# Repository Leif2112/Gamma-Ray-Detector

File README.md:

# Gamma Ray Detector

Open-source SiPM + scintillator gamma-ray detector designed for CubeSat payloads and lab use. The project refines the Pi-Pico [Open Gamma Detector] into a higher-fidelity instrument with an upgraded TIA, low-noise photodiode bias, and temperature-compensated SiPM operation.

> **Project status:** electronics and simulations complete; prototype assembly and environmental testing outstanding.

## Project output
- **Space focus:** tailored for CubeSat constraints.  
- **Cleaner analogue front-end:** OPA355 TIA selected for faster slew and lower noise than OPA357.  
- **Stable SiPM bias:** LT3571-based photodiode bias supply with low ripple and temperature compensation strategy.  
- **Thermal robustness:** overvoltage held constant vs temperature to stabilise SiPM gain/PDE.

---

## High-level objectives

1. Develop a CubeSat-compatible system by enhancing the Pi-Pico DIY detector  
2. Build a working prototype  
3. Test detection performance and space suitability

## Architecture

- [visual diagram]

- [ ] [Visuals]

## Features

- [ ] [Features list]

## Hardware

- [ ] [Hardware description]

## Firmware

- [ ] [Firmware dir.]

## Authors and acknowledgment

If you use this project in academic work, please cite the MSc thesis and this repository:
Tinwell, L. (2023). Gamma Ray Detector (MSc Thesis, University of Surrey).

***

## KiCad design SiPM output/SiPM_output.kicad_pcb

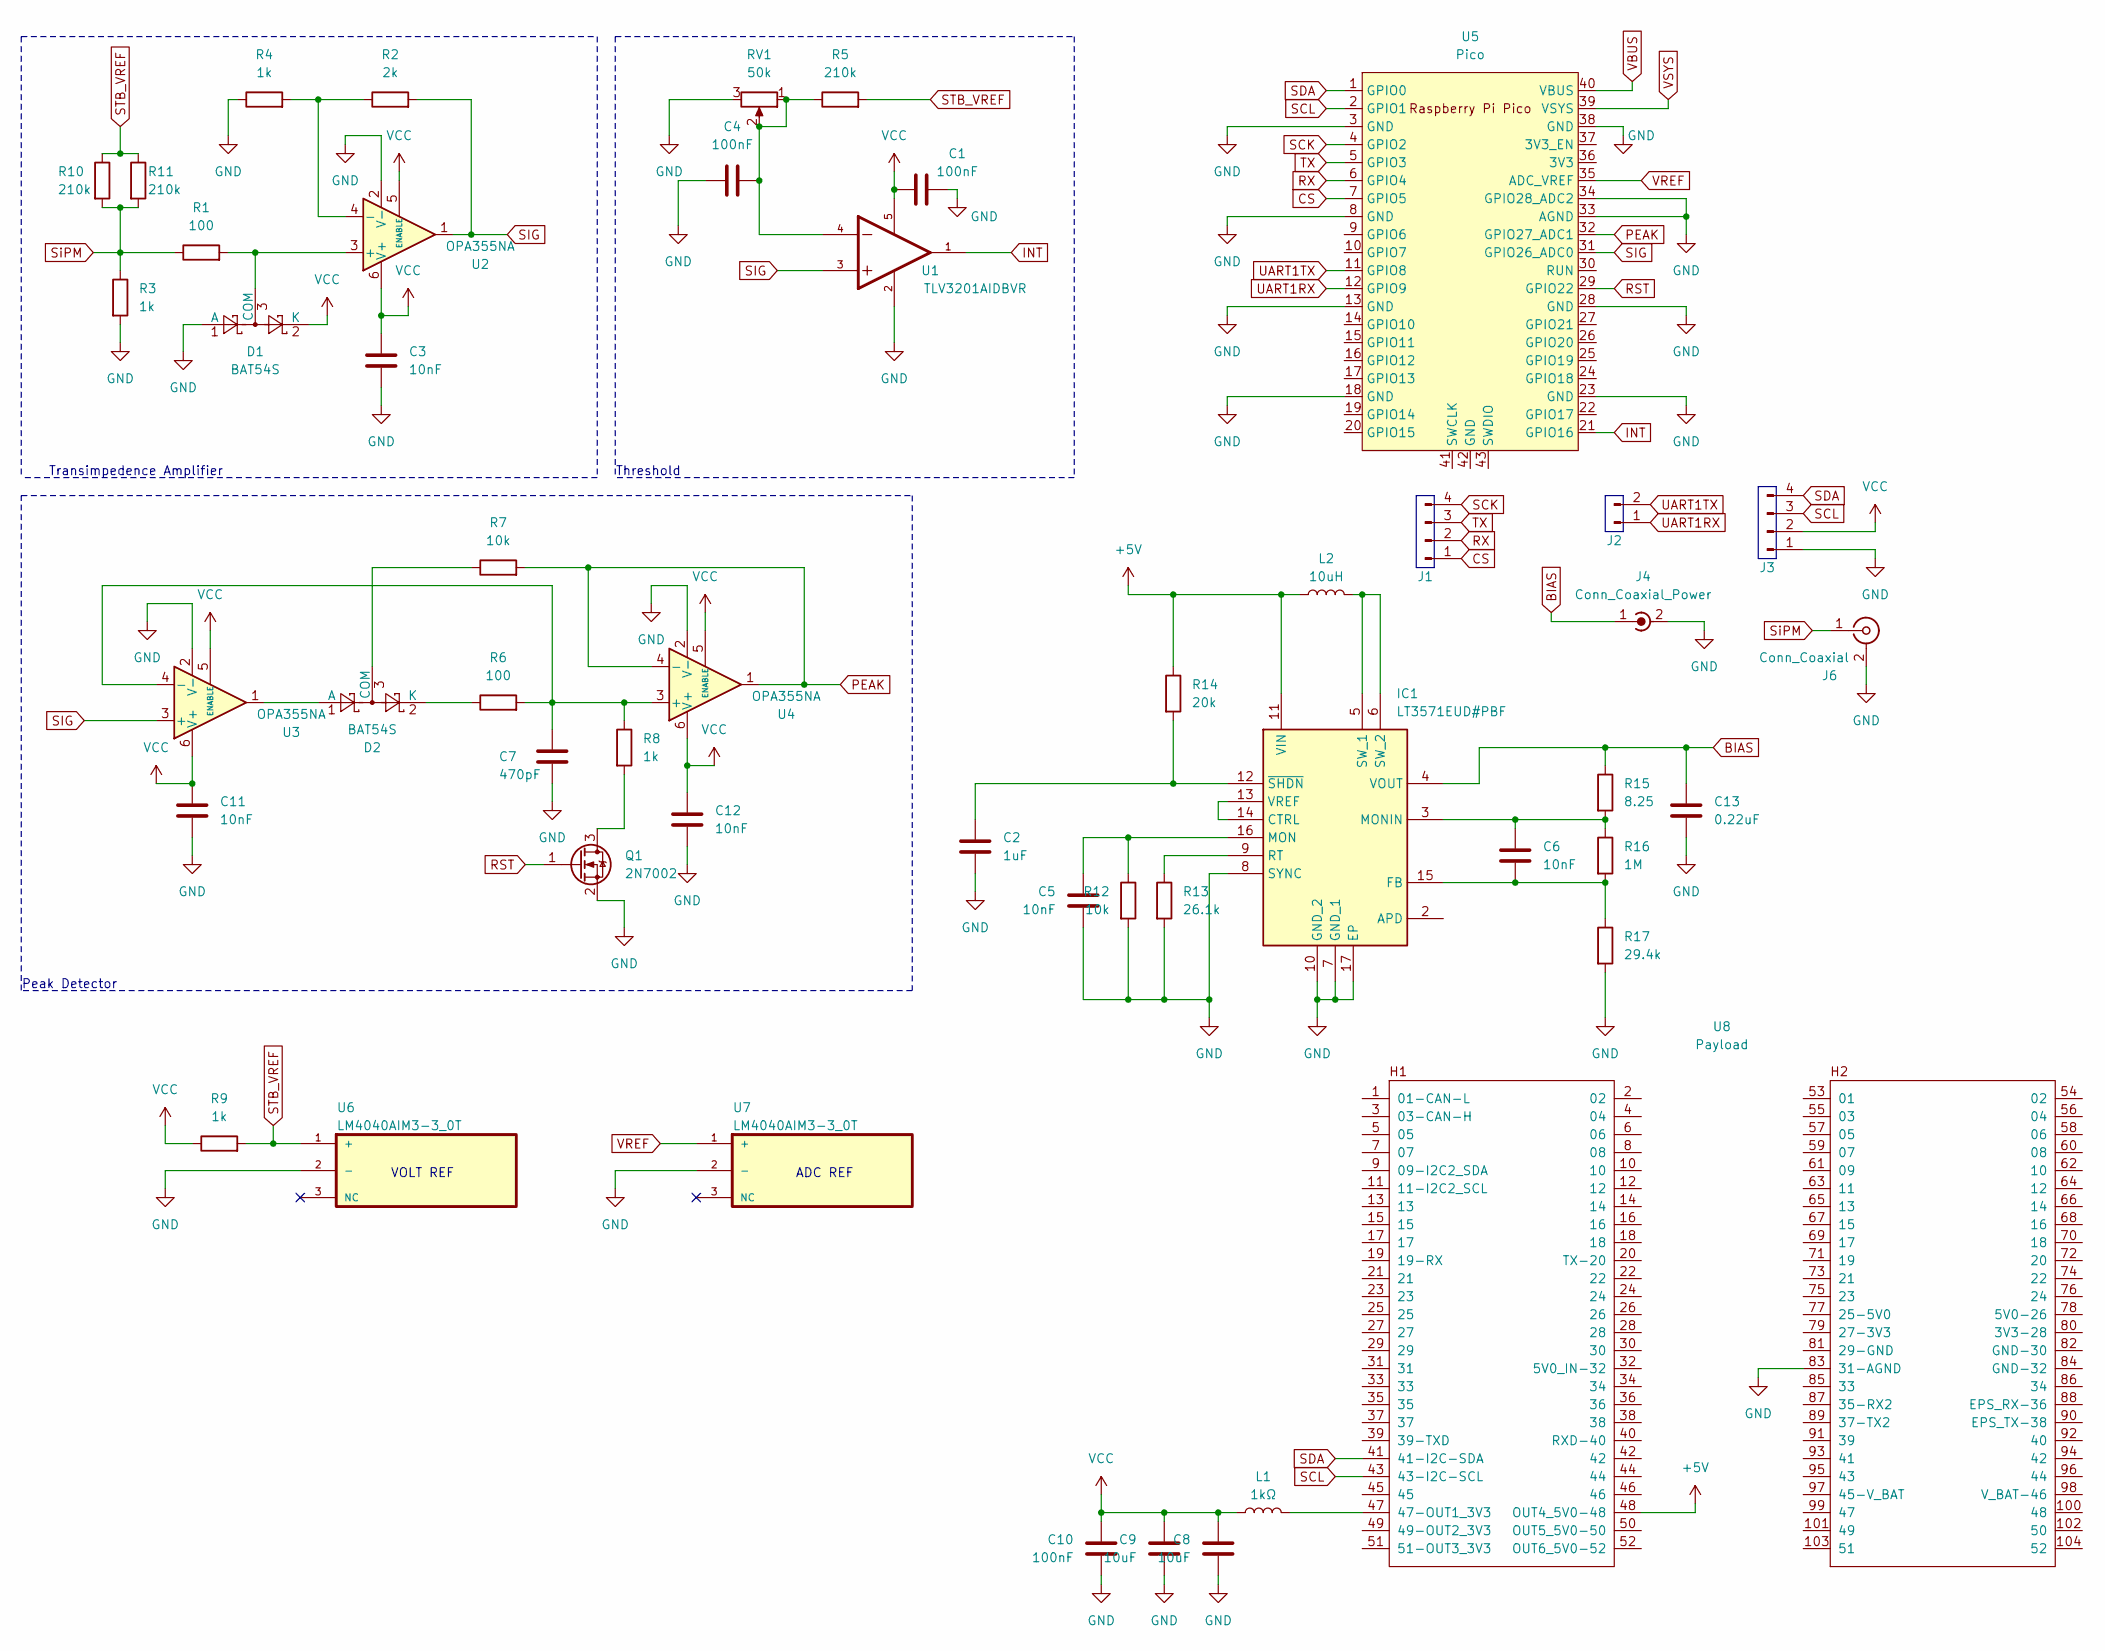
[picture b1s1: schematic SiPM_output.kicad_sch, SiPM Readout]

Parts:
C1, C4, C10: 100nF; C_0603_1608Metric
C2: 1uF; C_0603_1608Metric
C3, C5, C6, C11, C12: 10nF; C_0603_1608Metric
C7: 470pF; C_0603_1608Metric
C8, C9: 10uF; C_0603_1608Metric
C13: 0.22uF; C_0603_1608Metric
D1, D2: BAT54S; SOT-23
IC1: LT3571EUD#PBF; QFN50P300X300X80-17N-D
J1, J3: Conn_01x04_Pin; PinHeader_1x04_P2.54mm_Vertical
J2: Conn_01x02_Pin; PinHeader_1x02_P2.54mm_Vertical
J4: Conn_Coaxial_Power; SMA_Amphenol_132134-14_Vertical
J6: Conn_Coaxial; SMA_Amphenol_132134-14_Vertical
L1: 1kΩ; L_0603_1608Metric
L2: 10uH; L_Bourns_SRP7028A_7.3x6.6mm
Q1: 2N7002; SOT-23
R1, R6: 100; R_0603_1608Metric
R2: 2k; R_0603_1608Metric
R3, R4, R8, R9: 1k; R_0603_1608Metric
R5, R10, R11: 210k; R_0603_1608Metric
R7, R12: 10k; R_0603_1608Metric
R13: 26.1k; R_0603_1608Metric
R14: 20k; R_0603_1608Metric
R15: 8.25; R_0603_1608Metric
R16: 1M; R_0603_1608Metric
R17: 29.4k; R_0603_1608Metric
RV1: 50k; Potentiometer_Bourns_3296X_Horizontal
U1: TLV3201AIDBVR; SOT95P280X145-5N
U2, U3, U4: OPA355NA; SOT-23-6
U5: Pico; RPi_Pico_SMD_TH
U6, U7: LM4040AIM3-3_0T; SOT95P237X112-3N
U8: Payload; PC104-Standard

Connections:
+5V: IC1.11 (VIN), L2.1, R14.1, U8.48 (OUT4_5V0-48)
BIAS: C13.1, IC1.4 (VOUT), J4.1 (In), R15.1
CS: J1.1, U5.7 (GPIO5)
GND: C1.2, C2.2, C3.2, C4.1, C5.2, C7.2, C8.2, C9.2, C10.2, C11.2, C12.2, C13.2, D1.1 (A), IC1.7 (GND_1), IC1.8 (SYNC), IC1.10 (GND_2), IC1.17 (EP), J3.1, J4.2 (Ext), J6.2 (Ext), Q1.2 (S), R3.2, R4.1, R12.2, R13.2, R17.2, RV1.3, U1.2, U2.2 (V-), U3.2 (V-), U4.2 (V-), U5.3 (GND), U5.8 (GND), U5.13 (GND), U5.18 (GND), U5.23 (GND), U5.28 (GND), U5.33 (AGND), U5.34 (GPIO28_ADC2), U5.38 (GND), U6.2 (-), U7.2 (-), U8.83 (31-AGND)
INT: U1.1, U5.21 (GPIO16)
unnamed: C4.2, R5.1, RV1.1, RV1.2, U1.4
unnamed: D1.3 (COM), R1.2, U2.3 (+)
unnamed: D2.1 (A), U3.1
unnamed: D2.3 (COM), R7.1
unnamed: D2.2 (K), R6.1
unnamed: IC1.13 (VREF), IC1.14 (CTRL)
unnamed: C6.2, IC1.15 (FB), R16.2, R17.1
unnamed: C5.1, IC1.16 (MON), R12.1
unnamed: C6.1, IC1.3 (MONIN), R15.2, R16.1
unnamed: IC1.9 (RT), R13.1
unnamed: IC1.5 (SW_1), IC1.6 (SW_2), L2.2
unnamed: C2.1, IC1.12 (~SHDN), R14.2
unnamed: Q1.3 (D), R8.2
unnamed: R2.1, R4.2, U2.4 (-)
unnamed: C7.1, R6.2, R8.1, U3.4 (-), U4.3 (+)
unnamed: L1.1, U8.47 (47-OUT1_3V3)
PEAK: R7.2, U4.1, U4.4 (-), U5.32 (GPIO27_ADC1)
RST: Q1.1 (G), U5.29 (GPIO22)
RX: J1.2, U5.6 (GPIO4)
SCK: J1.4, U5.4 (GPIO2)
SCL: J3.3, U5.2 (GPIO1), U8.43 (43-I2C-SCL)
SDA: J3.4, U5.1 (GPIO0), U8.41 (41-I2C-SDA)
SIG: R2.2, U1.3, U2.1, U3.3 (+), U5.31 (GPIO26_ADC0)
STB_VREF: R5.2, R9.2, R10.1, R11.1, U6.1 (+)
SiPM: J6.1 (In), R1.1, R3.1, R10.2, R11.2
TX: J1.3, U5.5 (GPIO3)
UART1RX: J2.1, U5.12 (GPIO9)
UART1TX: J2.2, U5.11 (GPIO8)
VBUS: U5.40 (VBUS)
VCC: C1.1, C3.1, C8.1, C9.1, C10.1, C11.1, C12.1, D1.2 (K), J3.2, L1.2, R9.1, U1.5, U2.5 (ENABLE), U2.6 (V+), U3.5 (ENABLE), U3.6 (V+), U4.5 (ENABLE), U4.6 (V+)
VREF: U5.35 (ADC_VREF), U7.1 (+)
VSYS: U5.39 (VSYS)

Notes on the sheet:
Threshold
VOLT REF
Transimpedence Amplifier
Peak Detector
ADC REF

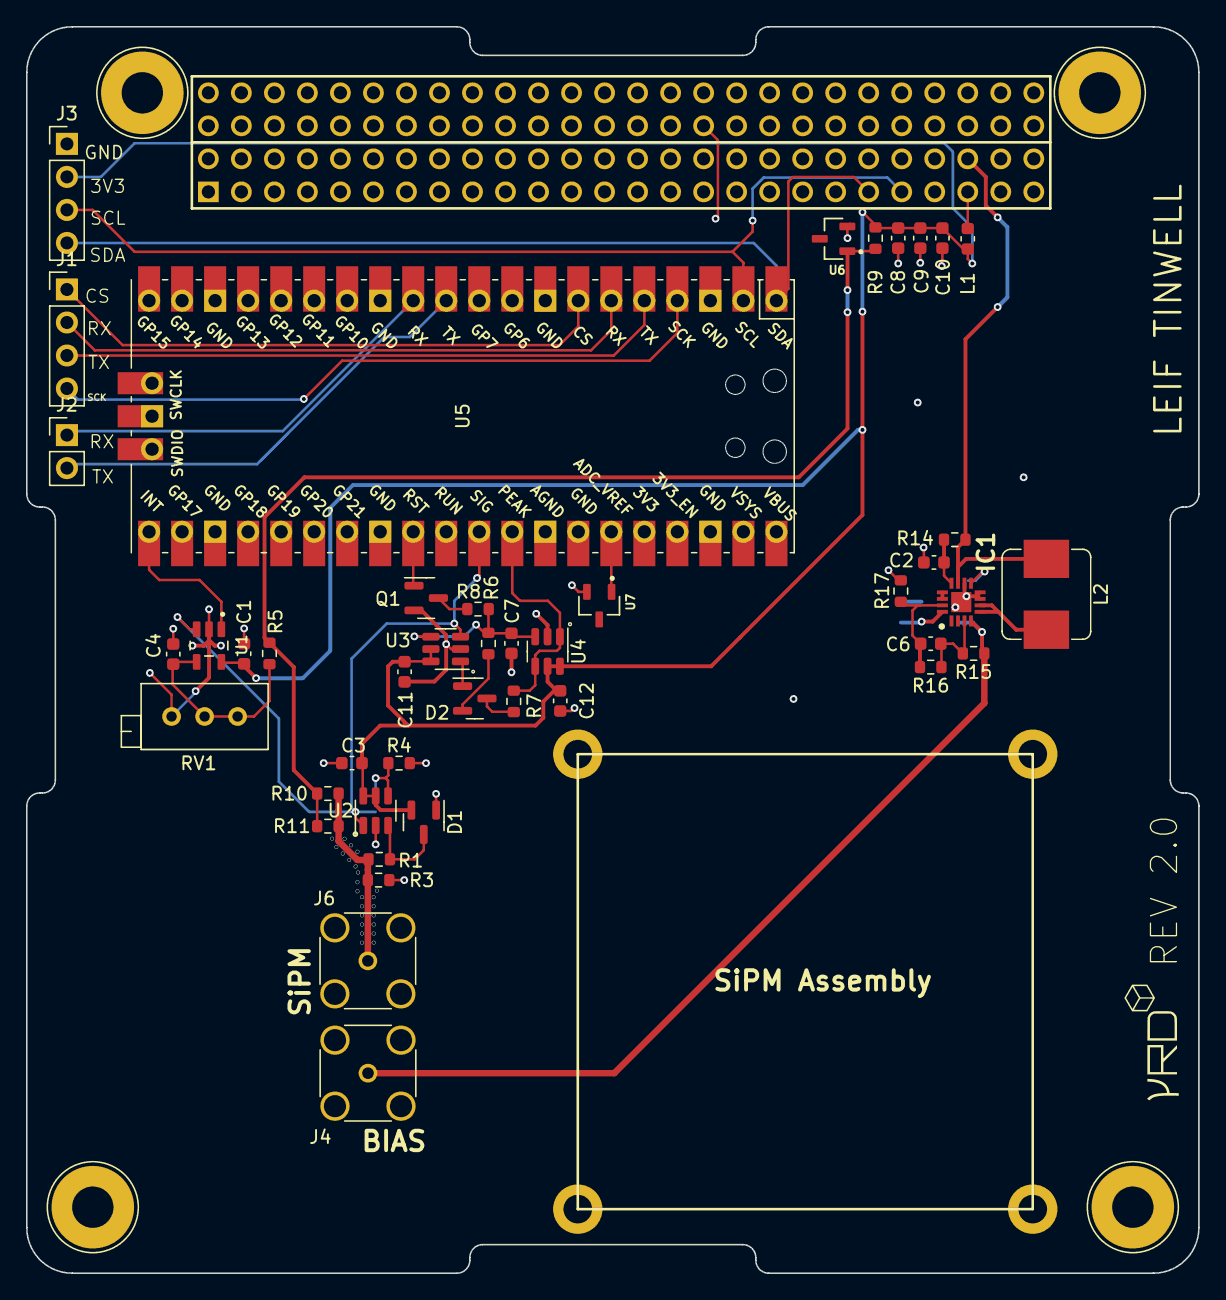
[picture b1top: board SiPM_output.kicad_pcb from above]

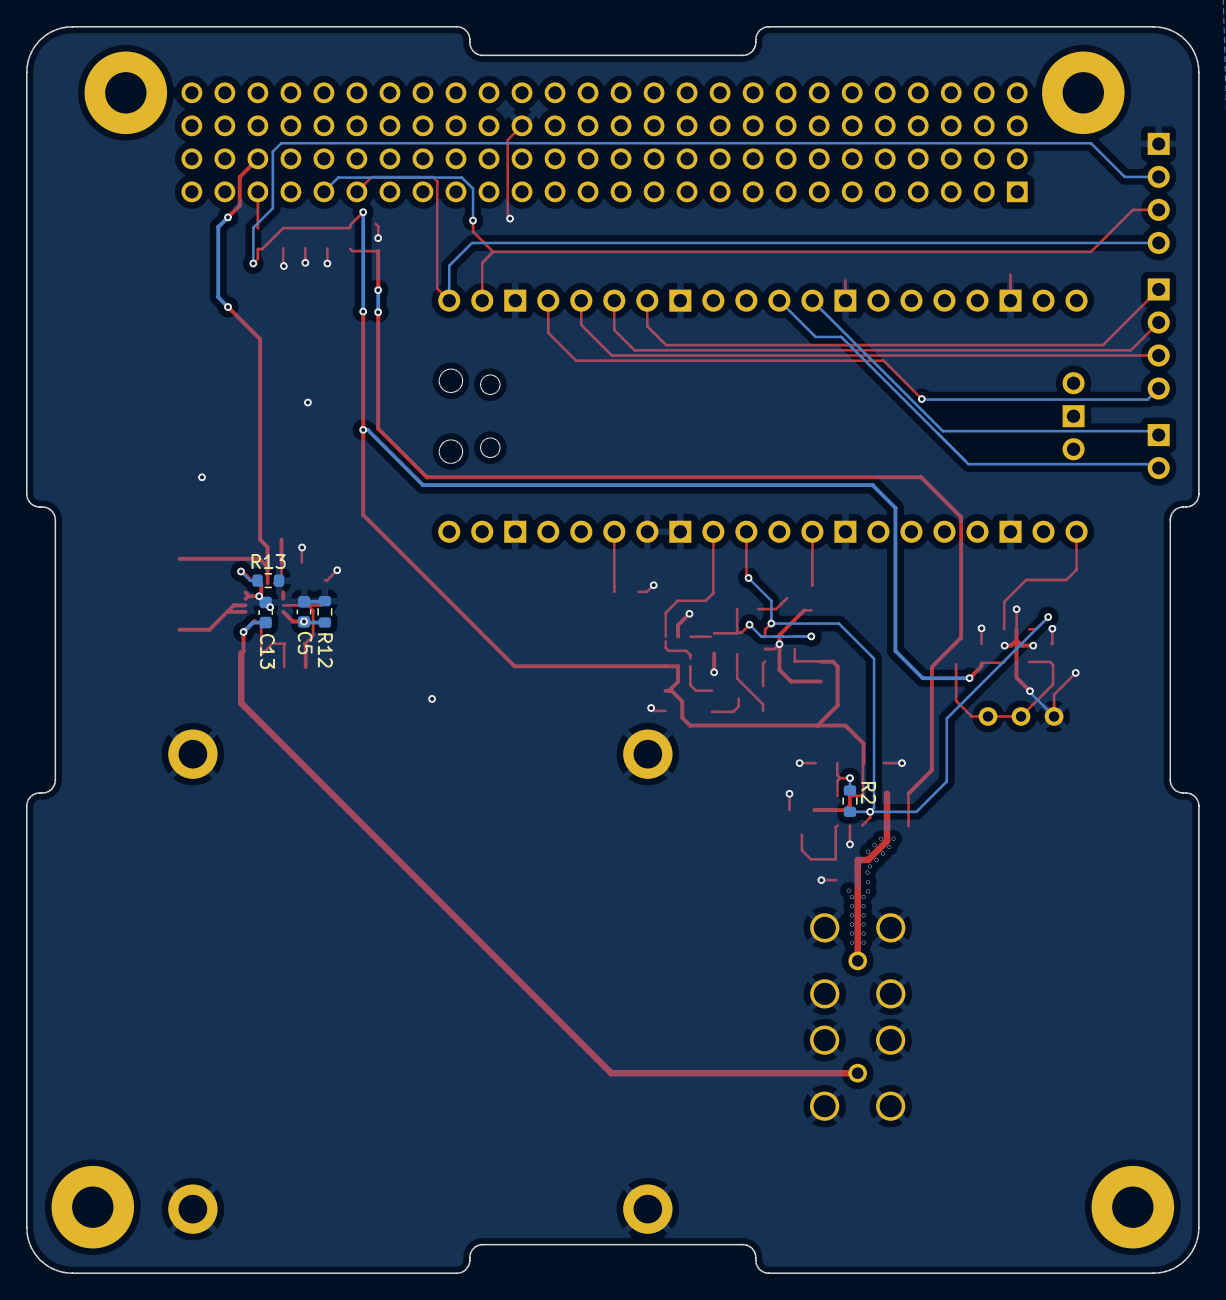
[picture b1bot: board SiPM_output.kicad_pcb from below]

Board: 2 copper layers, 90.2 x 95.9 mm, 50 parts (5 on the bottom side), 35 nets.

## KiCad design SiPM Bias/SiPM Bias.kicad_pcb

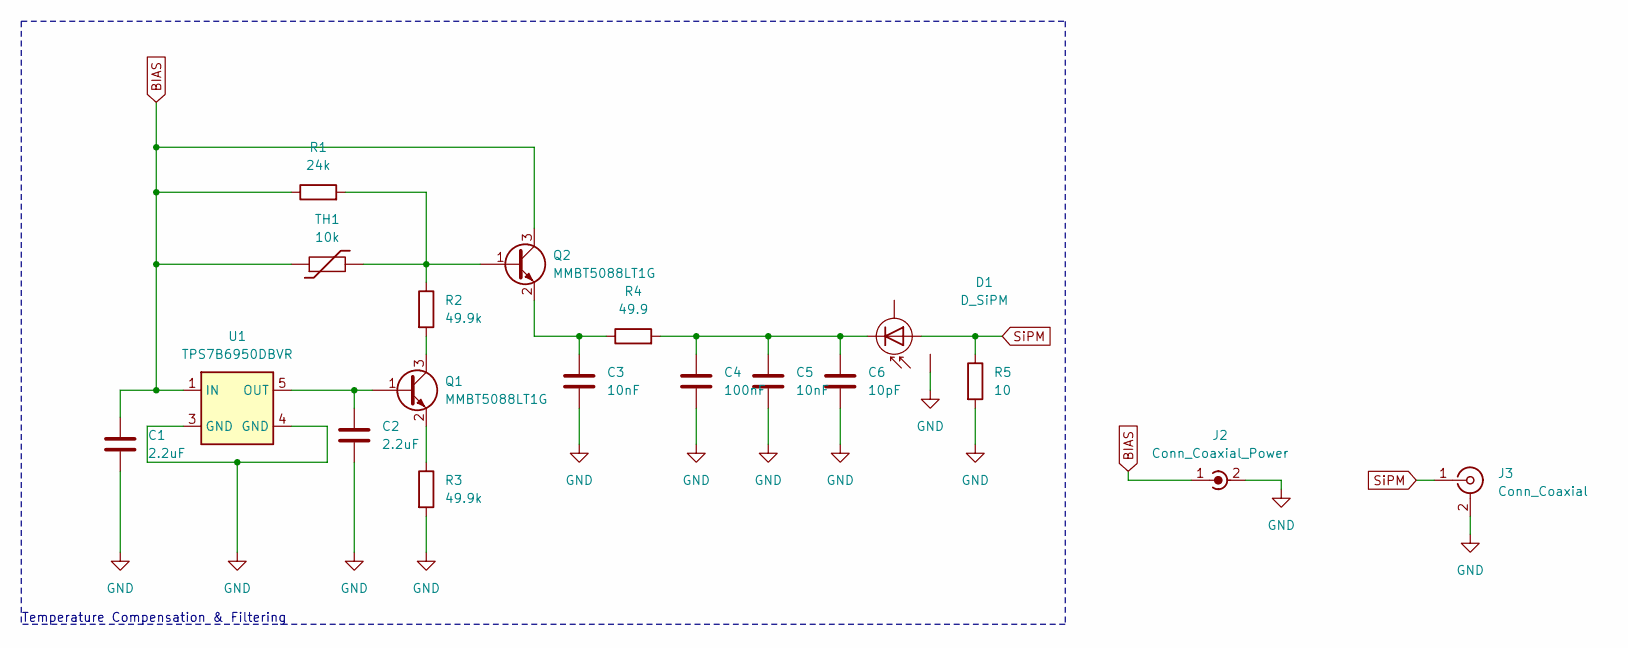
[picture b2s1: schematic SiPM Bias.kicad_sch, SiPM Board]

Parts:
C1, C2: 2.2uF; C_0603_1608Metric
C3, C5: 10nF; C_0603_1608Metric
C4: 100nF; C_0603_1608Metric
C6: 10pF; C_0603_1608Metric
D1: D_SiPM; MICROFC-60035
J2: Conn_Coaxial_Power; SMA_Amphenol_132134-14_Vertical
J3: Conn_Coaxial; SMA_Amphenol_132134-14_Vertical
Q1, Q2: MMBT5088LT1G; SOT-23-3
R1: 24k; R_0603_1608Metric
R2, R3: 49.9k; R_0603_1608Metric
R4: 49.9; R_0603_1608Metric
R5: 10; R_0603_1608Metric
TH1: 10k; R_0603_1608Metric
U1: TPS7B6950DBVR; SOT-23-5

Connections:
BIAS: C1.1, J2.1 (In), Q2.3 (C), R1.1, TH1.1, U1.1 (IN)
GND: C1.2, C2.2, C3.2, C4.2, C5.2, C6.2, D1.4 (G), J2.2 (Ext), J3.2 (Ext), R3.2, R5.2, U1.3 (GND), U1.4 (GND)
unnamed: C4.1, C5.1, C6.1, D1.3 (C), R4.2
unnamed: C2.1, Q1.1 (B), U1.5 (OUT)
unnamed: Q1.3 (C), R2.2
unnamed: Q1.2 (E), R3.1
unnamed: Q2.1 (B), R1.2, R2.1, TH1.2
unnamed: C3.1, Q2.2 (E), R4.1
SiPM: D1.1 (A), J3.1 (In), R5.1

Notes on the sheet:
Temperature Compensation & Filtering

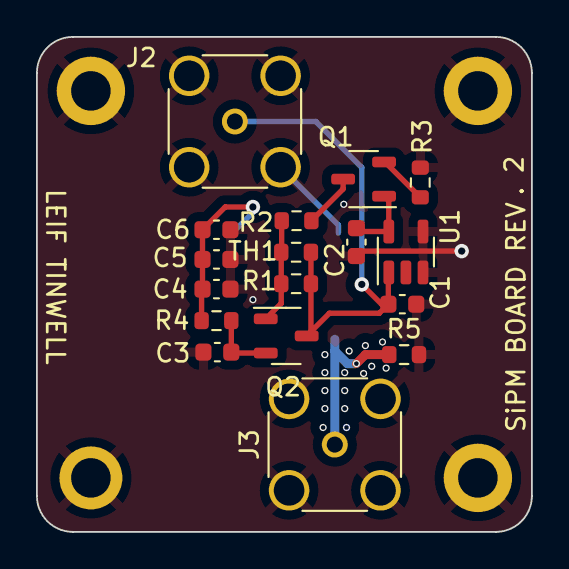
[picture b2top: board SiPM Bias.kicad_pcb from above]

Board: 2 copper layers, 27.5 x 27.5 mm, 18 parts (1 on the bottom side), 9 nets.

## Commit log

2025-09-03 initialise repo and upload /documents
2025-09-03 Upload SiPM Bias
2025-09-03 Upload SiPM output
